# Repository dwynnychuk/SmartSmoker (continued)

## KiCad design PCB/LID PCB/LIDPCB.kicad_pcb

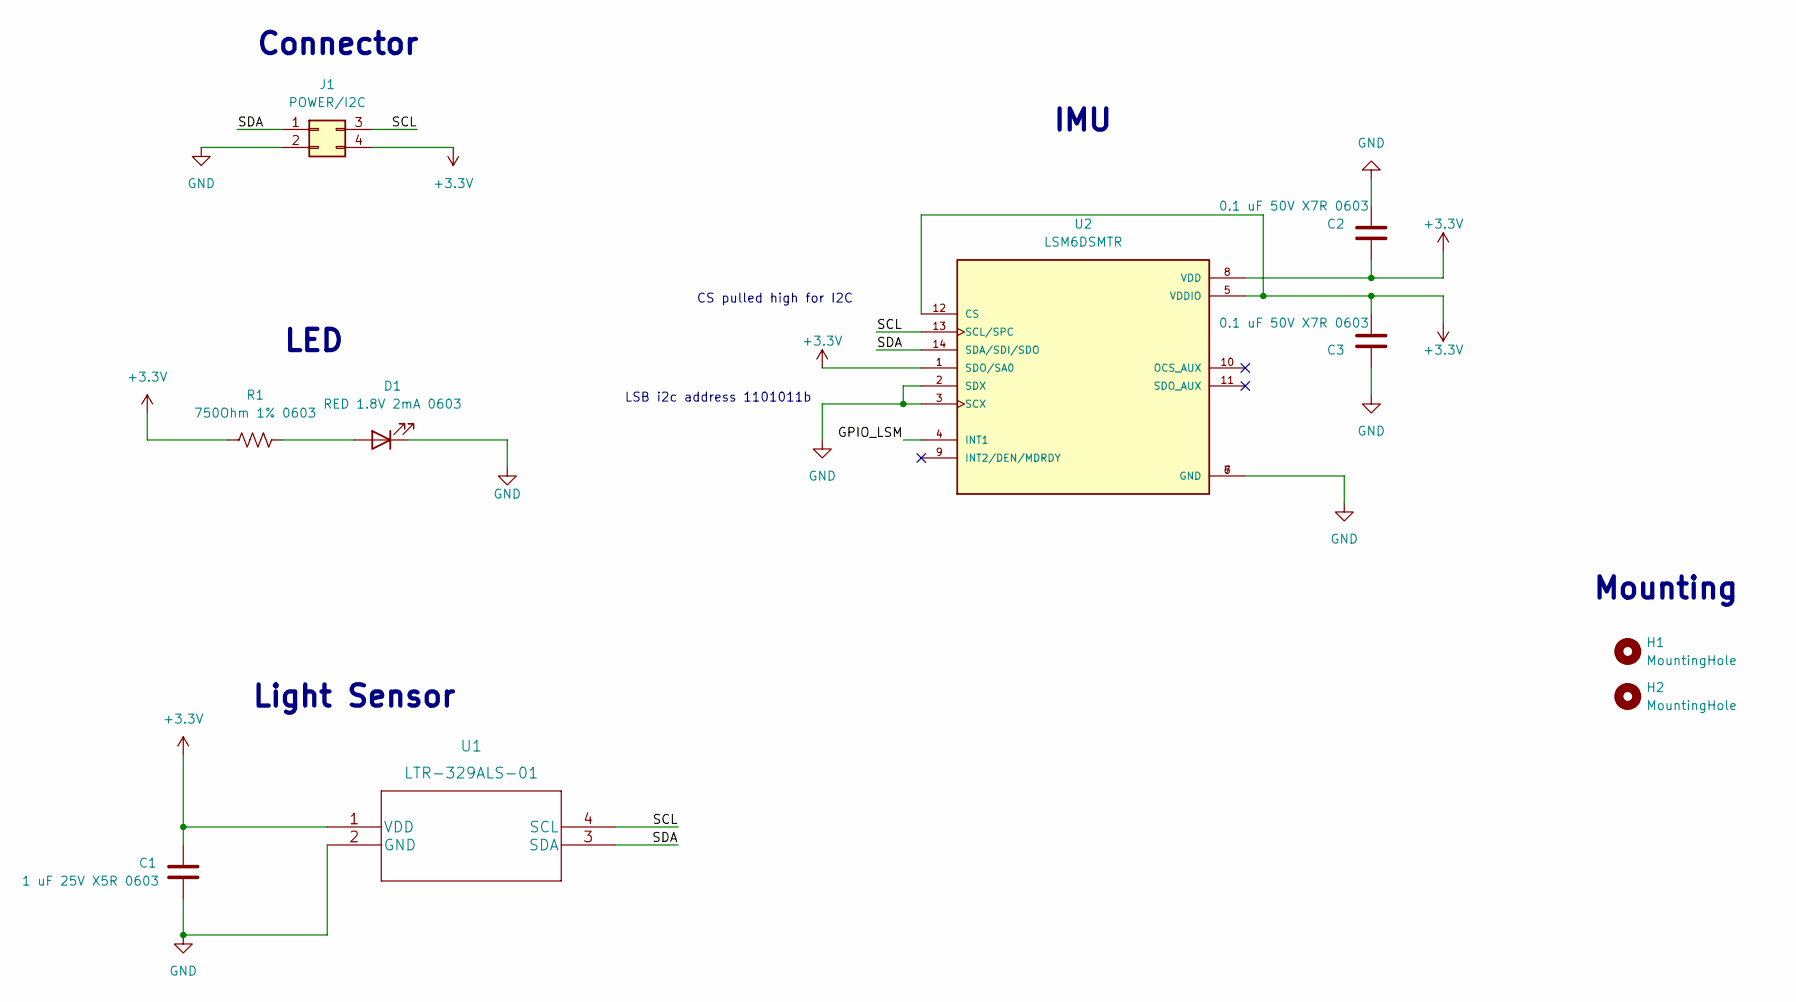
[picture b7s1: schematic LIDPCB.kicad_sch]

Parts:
C1: 1 uF 25V X5R 0603; C_0603_1608Metric; Manufacturer Part Number CL10A105KA8NNNC
C2, C3: 0.1 uF 50V X7R 0603; C_0603_1608Metric; Manufacturer Part Number CL10B104KB8NNWC
D1: RED 1.8V 2mA 0603; LED_0603_1608Metric; Manufacturer Part Number CSL1901UW1
H1, H2: MountingHole; MountingHole_3.2mm_M3_DIN965_Pad
J1: POWER/I2C; Molex_Micro-Fit_3.0_43045-0400_2x02_P3.00mm_Horizontal; Manufacturer Part Number 0430450400
R1: 750Ohm 1% 0603; R_0603_1608Metric; Manufacturer Part Number RC0603FR-07750RL
U1: LTR-329ALS-01; Manufacturer Part Number LTR-329ALS-01
U2: LSM6DSMTR; PQFN50P300X250X86-14N; PARTREV Rev 7

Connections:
+3.3V: C1.1, C2.2, C3.2, J1.4, R1.2, U1.1 (VDD), U2.1 (SDO/SA0), U2.5 (VDDIO), U2.8 (VDD), U2.12 (CS)
/GPIO_LSM: U2.4 (INT1)
/SCL: J1.3, U1.4 (SCL), U2.13 (SCL/SPC)
/SDA: J1.1, U1.3 (SDA), U2.14 (SDA/SDI/SDO)
GND: C1.2, C2.1, C3.1, D1.1 (K), J1.2, U1.2 (GND), U2.2 (SDX), U2.3 (SCX), U2.6 (GND), U2.7 (GND)
unnamed: D1.2 (A), R1.1

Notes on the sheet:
IMU
LSB i2c address 1101011b
CS pulled high for I2C
Connector
Mounting
LED
Light Sensor

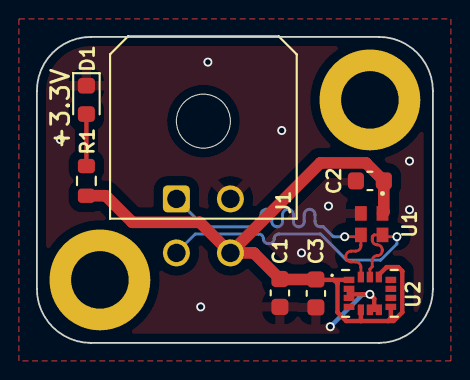
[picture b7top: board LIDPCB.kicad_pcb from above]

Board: 2 copper layers, 22.0 x 17.0 mm, 10 parts (0 on the bottom side), 5 nets.

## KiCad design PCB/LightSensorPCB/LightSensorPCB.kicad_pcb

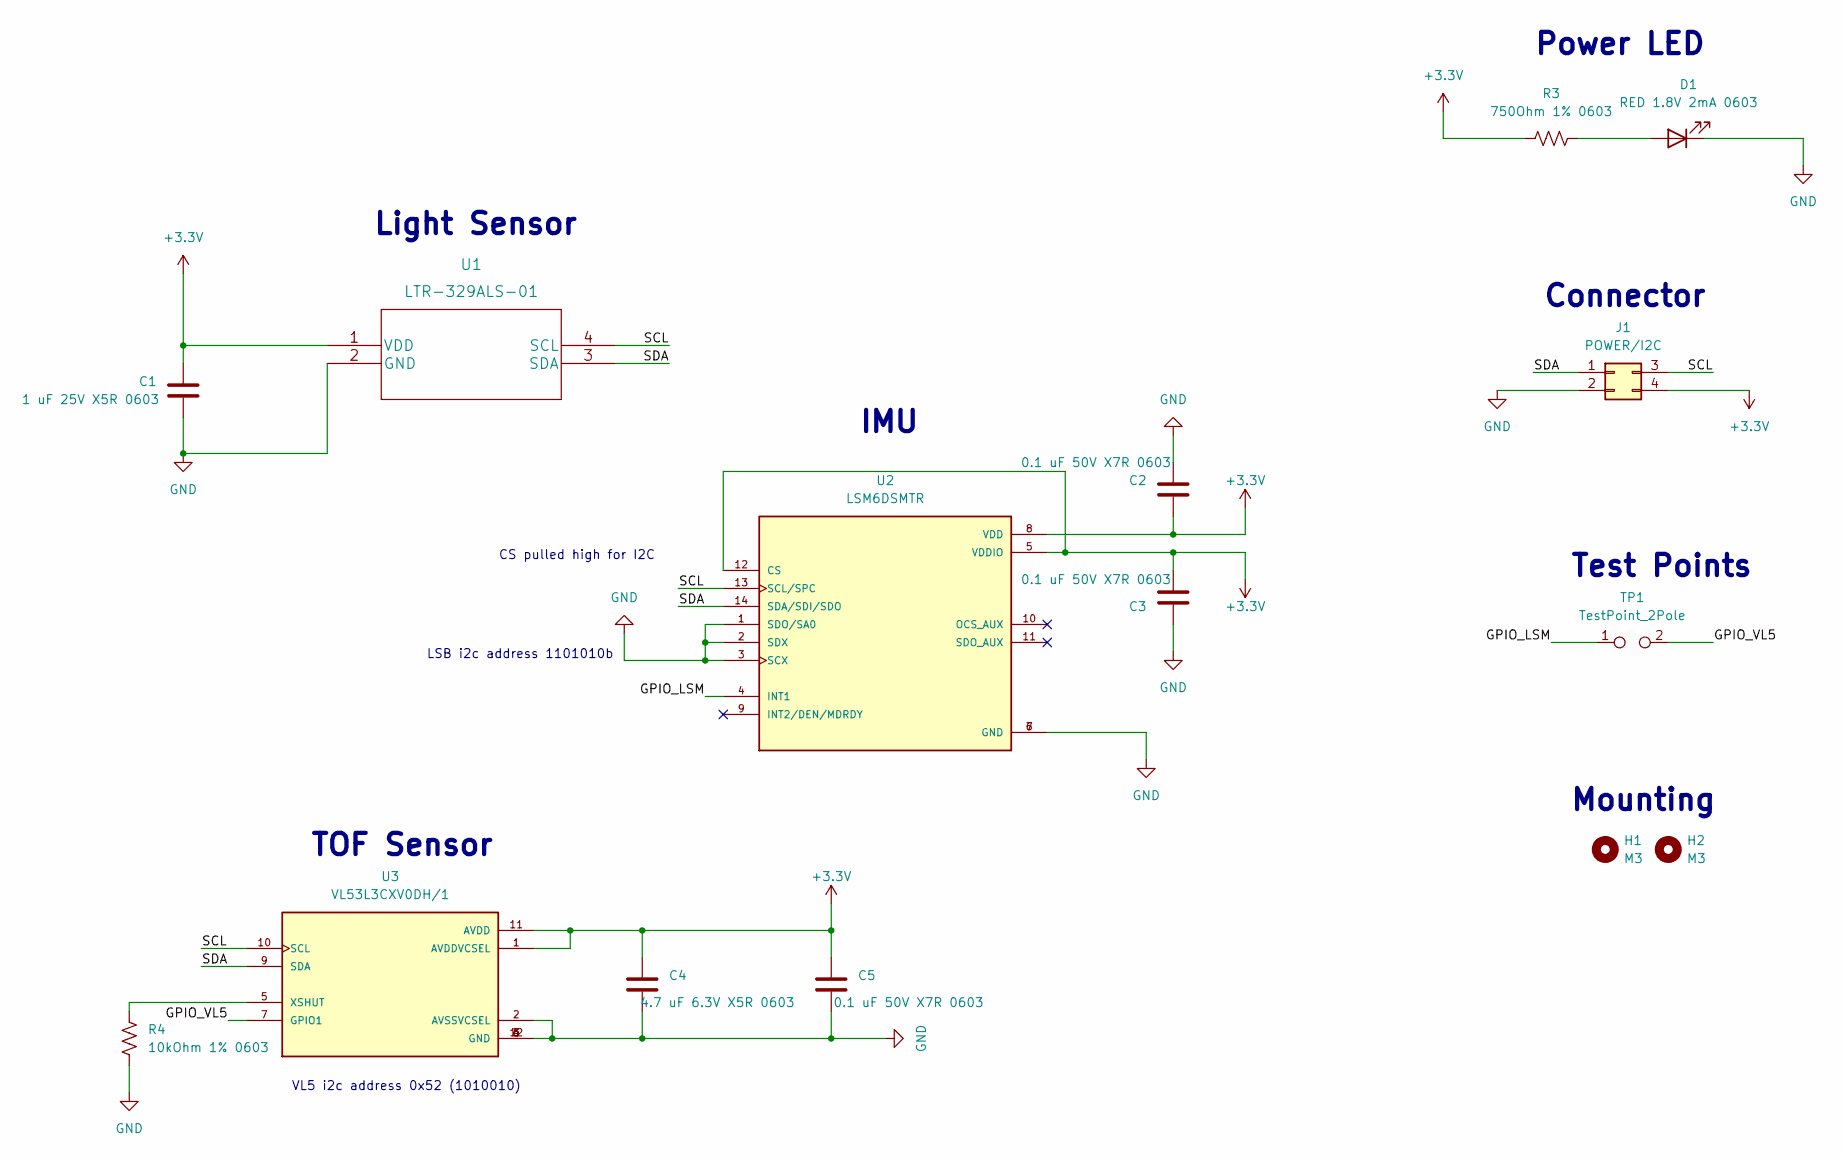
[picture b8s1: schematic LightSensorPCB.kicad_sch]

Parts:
C1: 1 uF 25V X5R 0603; C_0603_1608Metric; Manufacturer Part Number CL10A105KA8NNNC
C2, C3, C5: 0.1 uF 50V X7R 0603; C_0603_1608Metric; Manufacturer Part Number CL10B104KB8NNWC
C4: 4.7 uF 6.3V X5R 0603; C_0603_1608Metric; Manufacturer Part Number CL10A475KQ8NNNC
D1: RED 1.8V 2mA 0603; LED_0603_1608Metric; Manufacturer Part Number CSL1901UW1
H1, H2: M3; MountingHole_3.2mm_M3_DIN965_Pad
J1: POWER/I2C; Molex_Micro-Fit_3.0_43045-0400_2x02_P3.00mm_Horizontal; Manufacturer Part Number 0430450400
R3: 750Ohm 1% 0603; R_0603_1608Metric; Manufacturer Part Number RC0603FR-07750RL
R4: 10kOhm 1% 0603; R_0603_1608Metric; Manufacturer Part Number RNCP0603FTD10K0
TP1: TestPoint_2Pole; PinHeader_1x02_P2.54mm_Vertical
U1: LTR-329ALS-01; Manufacturer Part Number LTR-329ALS-01
U2: LSM6DSMTR; PQFN50P300X250X86-14N; PARTREV Rev 7
U3: VL53L3CXV0DH/1; XDCR_VL53L3CXV0DH/1; PARTREV 2

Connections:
+3.3V: C1.1, C2.2, C3.2, C4.1, C5.1, J1.4, R3.2, U1.1 (VDD), U2.5 (VDDIO), U2.8 (VDD), U2.12 (CS), U3.1 (AVDDVCSEL), U3.11 (AVDD)
/GPIO_LSM: TP1.1, U2.4 (INT1)
/GPIO_VL5: TP1.2, U3.7 (GPIO1)
/SCL: J1.3, U1.4 (SCL), U2.13 (SCL/SPC), U3.10 (SCL)
/SDA: J1.1, U1.3 (SDA), U2.14 (SDA/SDI/SDO), U3.9 (SDA)
GND: C1.2, C2.1, C3.1, C4.2, C5.2, D1.1 (K), J1.2, R4.1, U1.2 (GND), U2.1 (SDO/SA0), U2.2 (SDX), U2.3 (SCX), U2.6 (GND), U2.7 (GND), U3.2 (AVSSVCSEL), U3.3 (GND), U3.4 (GND), U3.6 (GND), U3.12 (GND)
unnamed: D1.2 (A), R3.1
unnamed: R4.2, U3.5 (XSHUT)

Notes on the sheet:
Mounting
CS pulled high for I2C
TOF Sensor
Test Points
Light Sensor
VL5 i2c address 0x52 (1010010)
LSB i2c address 1101010b
Connector
Power LED
IMU

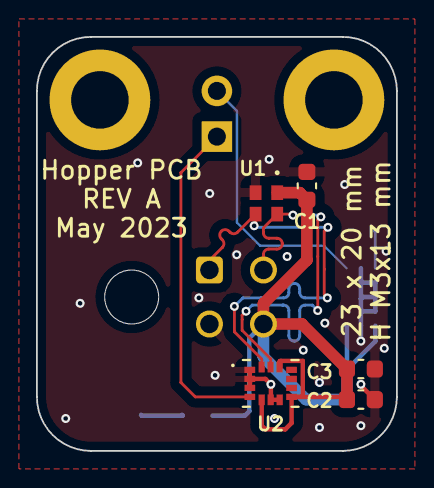
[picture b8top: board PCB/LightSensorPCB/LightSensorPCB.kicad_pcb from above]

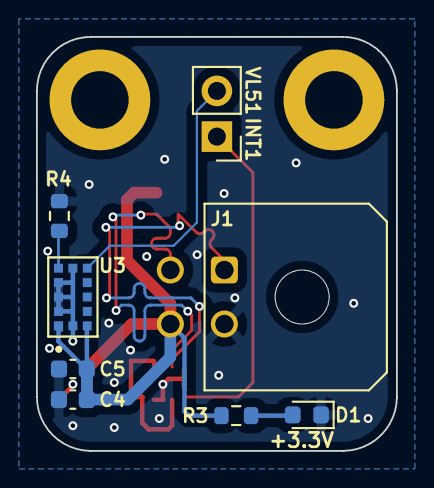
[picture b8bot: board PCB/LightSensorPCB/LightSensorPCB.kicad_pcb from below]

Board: 2 copper layers, 20.0 x 23.0 mm, 15 parts (8 on the bottom side), 8 nets.

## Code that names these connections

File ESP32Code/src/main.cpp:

#include <Arduino.h>
#include <Wire.h>

#include "Telemetry.h"
#include "GrillTypes.h"
#include "EncoderEvent.h"

#include "IMU.h"
#include "LightSensor.h"
#include "RTD.h"
#include "Thermocouple.h"
#include "SensorManager.h"

#include "AugerController.h"
#include "FanController.h"
#include "IgnitorController.h"
#include "PID.h"

#include "DisplayController.h"
#include "EncoderInput.h"
#include "StateMachine.h"

// ── Pin assignments ─────────────
#define PIN_AUGER        25
#define PIN_FAN          26
#define PIN_IGNITOR      27

#define PIN_RTD_PLUS     34   // ADC1 pin
#define PIN_RTD_MINUS    35   // ADC1 pin
#define RTD_VREF         3.3f
#define RTD_RREF         1000.0f

#define TC_CLK           18
#define TC_CS            5
#define TC_MISO          19

#define IMU_I2C_ADDR     0xD7   // LSM6DSR address

#define LIGHT_I2C_ADDR   0x29   // LTR-329 address

#define PIN_ENC_CLK      32
#define PIN_ENC_DT       33
#define PIN_ENC_SW       14

// PID tuning — placeholder values
#define PID_KP           0.02f
#define PID_KI           0.0005f
#define PID_KD           0.01f

// ── Shared state ─────────────────────────────────────────────────────────
Telemetry telemetry;

// ── Sensors ──────────────────────────────────────────────────────────────
IMU          imu(&Wire, IMU_I2C_ADDR);
LightSensor  lightSensor(LIGHT_I2C_ADDR);
RTD          rtd(PIN_RTD_PLUS, PIN_RTD_MINUS, RTD_VREF, RTD_RREF);
Thermocouple thermocouple(TC_CLK, TC_CS, TC_MISO);

SensorManager sensors(imu, lightSensor, rtd, thermocouple, telemetry);

// ── Loads ────────────────────────────────────────────────────────────────
AugerController   auger(PIN_AUGER);
FanController     fan(PIN_FAN);
IgnitorController ignitor(PIN_IGNITOR);

// ── Control / UI ─────────────────────────────────────────────────────────
PID               pid(PID_KP, PID_KI, PID_KD);
DisplayController display;
EncoderInput      encoder(PIN_ENC_CLK, PIN_ENC_DT, PIN_ENC_SW);

StateMachine stateMachine(auger, fan, ignitor, pid, display);

void setup() {
    Serial.begin(115200);
    Wire.begin();

    if (!sensors.begin()) {
        Serial.println("WARNING: one or more sensors failed to init");
        // Intentionally continue rather than halt — StateMachine's
        // _sensorFault() guard will catch bad readings and go to ERROR.
    }

    if (!display.begin()) {
        Serial.println("WARNING: display failed to init");
    }

    encoder.begin();

    Serial.println("Smoker controller ready.");
}

void loop() {
    sensors.update();
    EncoderEvent enc = encoder.read();

    stateMachine.tick(sensors.getData(), enc);

    // Small delay to avoid hammering I2C/ADC every cycle.
    // UPDATE_INTERVAL_MS gate so this doesn't need to be precise.
    delay(50);
}

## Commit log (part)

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2023-02-03 Added PCB Files
2023-02-05 Added C++ Files
2023-02-05 Added C++ code
2023-02-05 Accelerometer Code
2023-02-06 Accelerometer reading values, seems incorrect. Refactoring
2023-02-06 Accelerometer refactored, need to calibrate
2023-02-06 Accelerometer working, issue with calibration
2023-02-08 Calibration not working and deleted
2023-02-08 Preparation for thermocouple integration
2023-02-11 SPI ambient temp integration
2023-02-11 functional thermocouple with I2C
2023-02-12 photoresistor functional
2023-02-12 PCB for light sensor started
2023-02-14 Light detection PCB
2023-02-15 Light detection PCB finished
2023-02-16 Added ESP32 board pcb files
2023-03-05 Start BLE implementation
2023-03-05 BLE hello world
2023-03-07 BLE functional hello world
2023-03-07 refactor ble
2023-05-22 Significant PCB progress
2023-05-25 PCB layout done
2023-05-26 46 traces left for routing main pcb
2023-05-27 Main PCB ready for review
2023-05-28 LID PCB ready for review
2023-05-28 Main pcb reviewed
2023-05-30 3x PCB ready for gerberization
2023-05-30 3x PCB gerberd
2023-06-01 MOV added to PCB1
2023-06-02 3x PCB ordered
2023-06-27 Create README.md
    Updated readme
2023-06-27 Update README.md
    Readme updates
2023-07-22 Test on custom pcb initial
2023-07-22 blink works on custom pcb
2023-07-22 truth table for multiplexer
2023-07-22 code cleanup and begin to read output of thermocouples
2023-07-22 error in temp reading
2023-07-23 functional reading from LTR light sensor
2023-07-23 LTR sensor cleaned up
2023-07-29 add ToF library
2023-07-29 Max31855 and IO libraries added
2023-07-29 Temperature sensing working with new method, using MAX library. MUX stuck on OUT3, need to troubleshoot. Logic analizer reading consistent reading across mux
2023-07-29 MUX issue fixed
2023-07-29 Update README.md
    Added suggested changes for next hardware revision
2023-07-29 cleanup of temperature code
2023-07-29 LSM libraries added
2023-07-29 IMU works for hopper
2023-07-29 LID imu functional, issue with address for I2C forgetting read/write bit
2023-07-29 Both IMUs, light sensor, and temperature sensor functional
2023-08-01 Started Hardware Rev B
2023-08-01 Added suggestions to Hardware Rev B
2023-08-02 Hardware Rev B in progress
2023-08-06 Hardware Rev B development
2023-08-06 Hardware Rev B development - missing relays
2023-08-07 Hardware Rev B development - found 2/3 SSRs
2023-08-09 Hardware Rev B development - 3/3 SSRs sourced
2023-08-10 Hardware Rev B development Relays and Rotary Encoder
2023-08-15 Rev B Hardware - organization of schematic and initial layout for board sizing
2023-11-19 Component changes, new relays
2023-11-19 Component changes, new ignitor relay - need to do supporting circuity
2023-11-19 Relay circuitry complete - snubber added to inductive loads
2024-01-08 BLE Testing, all else functional
2024-01-08 BLE able to connect to bluetooth app, data not publishing to computer. Only in serial monitor
2024-01-09 BLE able to connect and publish data to bluetooth app
2024-01-09 App bluetooth starting
2024-03-03 BLE service swift WIP
2024-03-04 BLE connect to app, data not pushing
2024-03-06 Rid power path selector, moving to or diode system for power path selection
2024-03-06 Powerpath development
2024-03-07 Moved from ORing diodes to power MUX as per TI recommendations
2024-03-08 Power Mux and rest of power systems designed and ready for layout
2024-03-08 Changed out connectors to AJ connectors
2024-03-08 Changed rotary encoder to incremental, nearly done design on rotary encoder
2024-03-12 Rotary dial complete
2024-03-13 SD card complete. All gpio full
2024-03-31 Begin layout Rev B PCB
2024-09-08 Add gui
2024-09-09 GUI filed generated
2024-09-11 cleanup
2024-09-11 added connection frame to gui
2024-09-12 Testing output to gui successful w/ hello world
2024-09-12 Add combobox for com port
2024-09-18 Logging buttons and functionality working
2024-09-19 Add connection logic for connecting to com port
2024-09-23 Cleanup cpp output for GUI integration
2024-09-30 Logging to file and gui functional
2024-09-30 Fix logging stop button
2024-10-03 Get logging working again
2024-10-03 Second temp logging working
2025-03-09 PCB schematic updates, added 5V power supply
2025-03-09 PCB schematic updates, Modified and fixed all power sheets
2025-03-11 PCB schematic updates, Added optoisolators for relay circuits
2025-03-11 PCB schematic updates, Find mosfet for relay on circuit
2025-03-14 PCB schematic updates, Relay Circuits Completed
2025-03-16 PCB schematic updates, Thermocouple connector sourced and updated
2025-03-16 PCB schematic updates, Screen and Probe jack updates
2025-03-16 PCB schematic updates, Rotary Encoder Updates
2025-03-17 PCB schematic updates, Change to smaller thermocouple mux
2025-03-19 PCB schematic updates, Reboot circuit fixed
2025-03-19 PCB schematic updates, Changed transistor on reboot to double
2025-03-19 PCB schematic updates, Cleanup and Add LEDS
2025-03-20 PCB schematic updates, Fix LED part number and clean up schematic. Added test points
2025-03-30 PCB schematic updates, Delete lid connections, add qwiic connectors
2025-03-30 PCB Layout - Begin Grouping of main PCB
2025-03-31 PCB Layout - Continue Grouping layout
2025-03-31 PCB Layout - Continue Grouping layout for relays
2025-04-09 PCB Layout - Set board outline and organize
2025-04-10 PCB Layout - Modify board layout and get relay circuit organized
2025-04-18 PCB Layout - Fix Usb footprint
2025-04-19 PCB Layout - Work on rotary footprint, change usb to horizontal
2025-04-20 PCB Layout
2025-04-20 PCB - Changed to Analog and Digital Board to solve interface headaches
2025-04-21 PCB - Rough Analog Layout
2025-04-21 PCB - Rough Analog Layout and probe jack change to RTD
2025-04-23 PCB - Lay out analog led and power filtering
2025-04-23 PCB - Lay out analog mostly complete. cad added
2025-05-04 PCB - Grouping for digital layout
2025-05-05 PCB - Digital layout nearly complete
2025-05-05 PCB - Digital layout complete
2025-05-08 PCB - Digital/analog layout complete - ready to review
2025-05-08 PCB - Digital CAD Finished
2025-05-09 PCB - Analog Routing Begin
2025-05-09 PCB - Analog AC routing first pass
2025-05-09 PCB - Analog AC routing half done
2025-05-10 PCB - Analog routing complete, need final review
2025-05-10 PCB - digital routing underway
2025-05-11 PCB - digital routing halfway done
2025-05-12 PCB - digital routing first pass done
2025-05-12 PCB - hopper pcb done routing ready for review
2025-05-13 PCB - Text edited, all ready for review
2025-05-13 PCB - Hopper PCB reviewed and gerbers generated
2025-05-14 PCB - Analog pcb under review and making minor mods - diode placement
2025-05-15 PCB - Analog pcb complete review and gerber generated
2025-05-20 PCB - gerbers generated and boms started
2025-05-25 PCB - consolidated BOM - Ordered Components
2025-05-26 CAD - Spacer for digital and analog boards
2025-05-30 CAD - Faceplate Rev 01
2026-04-07 create interface sensor class for general sensor handling
2026-04-07 Add ambient light sensor class based on main.cpp
2026-04-08 imu header file
2026-04-08 restructure and bug fixes in light sensor code
2026-04-08 IMU sensor updates
2026-04-08 Temperature based CPP improvements
2026-04-09 RTD class updates
2026-04-09 RTD class tidied up
2026-04-09 Refactor and add general load class
2026-04-10 Duty cycle load code complete
2026-04-10 Develop auger controller
2026-04-10 Finished load classes
2026-04-10 PID header complete
2026-04-16 PID math baseline
2026-04-16 PID complete'
2026-04-17 Added state machine, telemetry, and displaycontroller.h files
2026-05-29 State machine and display controller header additions
2026-05-31 bones for display controller.cpp
2026-05-31 display controller helper functions
2026-05-31 display controller helper functions complete
2026-05-31 Telemetry struct development
2026-05-31 Bug fixes and state machine development
2026-05-31 state machine development
2026-06-01 State machine and encoder work
2026-06-01 Encoder hold developemnt
2026-06-02 encoder input developement
2026-06-02 Add sensor manager to handle simultenous updates of all sensors, header complete
2026-06-03 Sensor manager cpp development
